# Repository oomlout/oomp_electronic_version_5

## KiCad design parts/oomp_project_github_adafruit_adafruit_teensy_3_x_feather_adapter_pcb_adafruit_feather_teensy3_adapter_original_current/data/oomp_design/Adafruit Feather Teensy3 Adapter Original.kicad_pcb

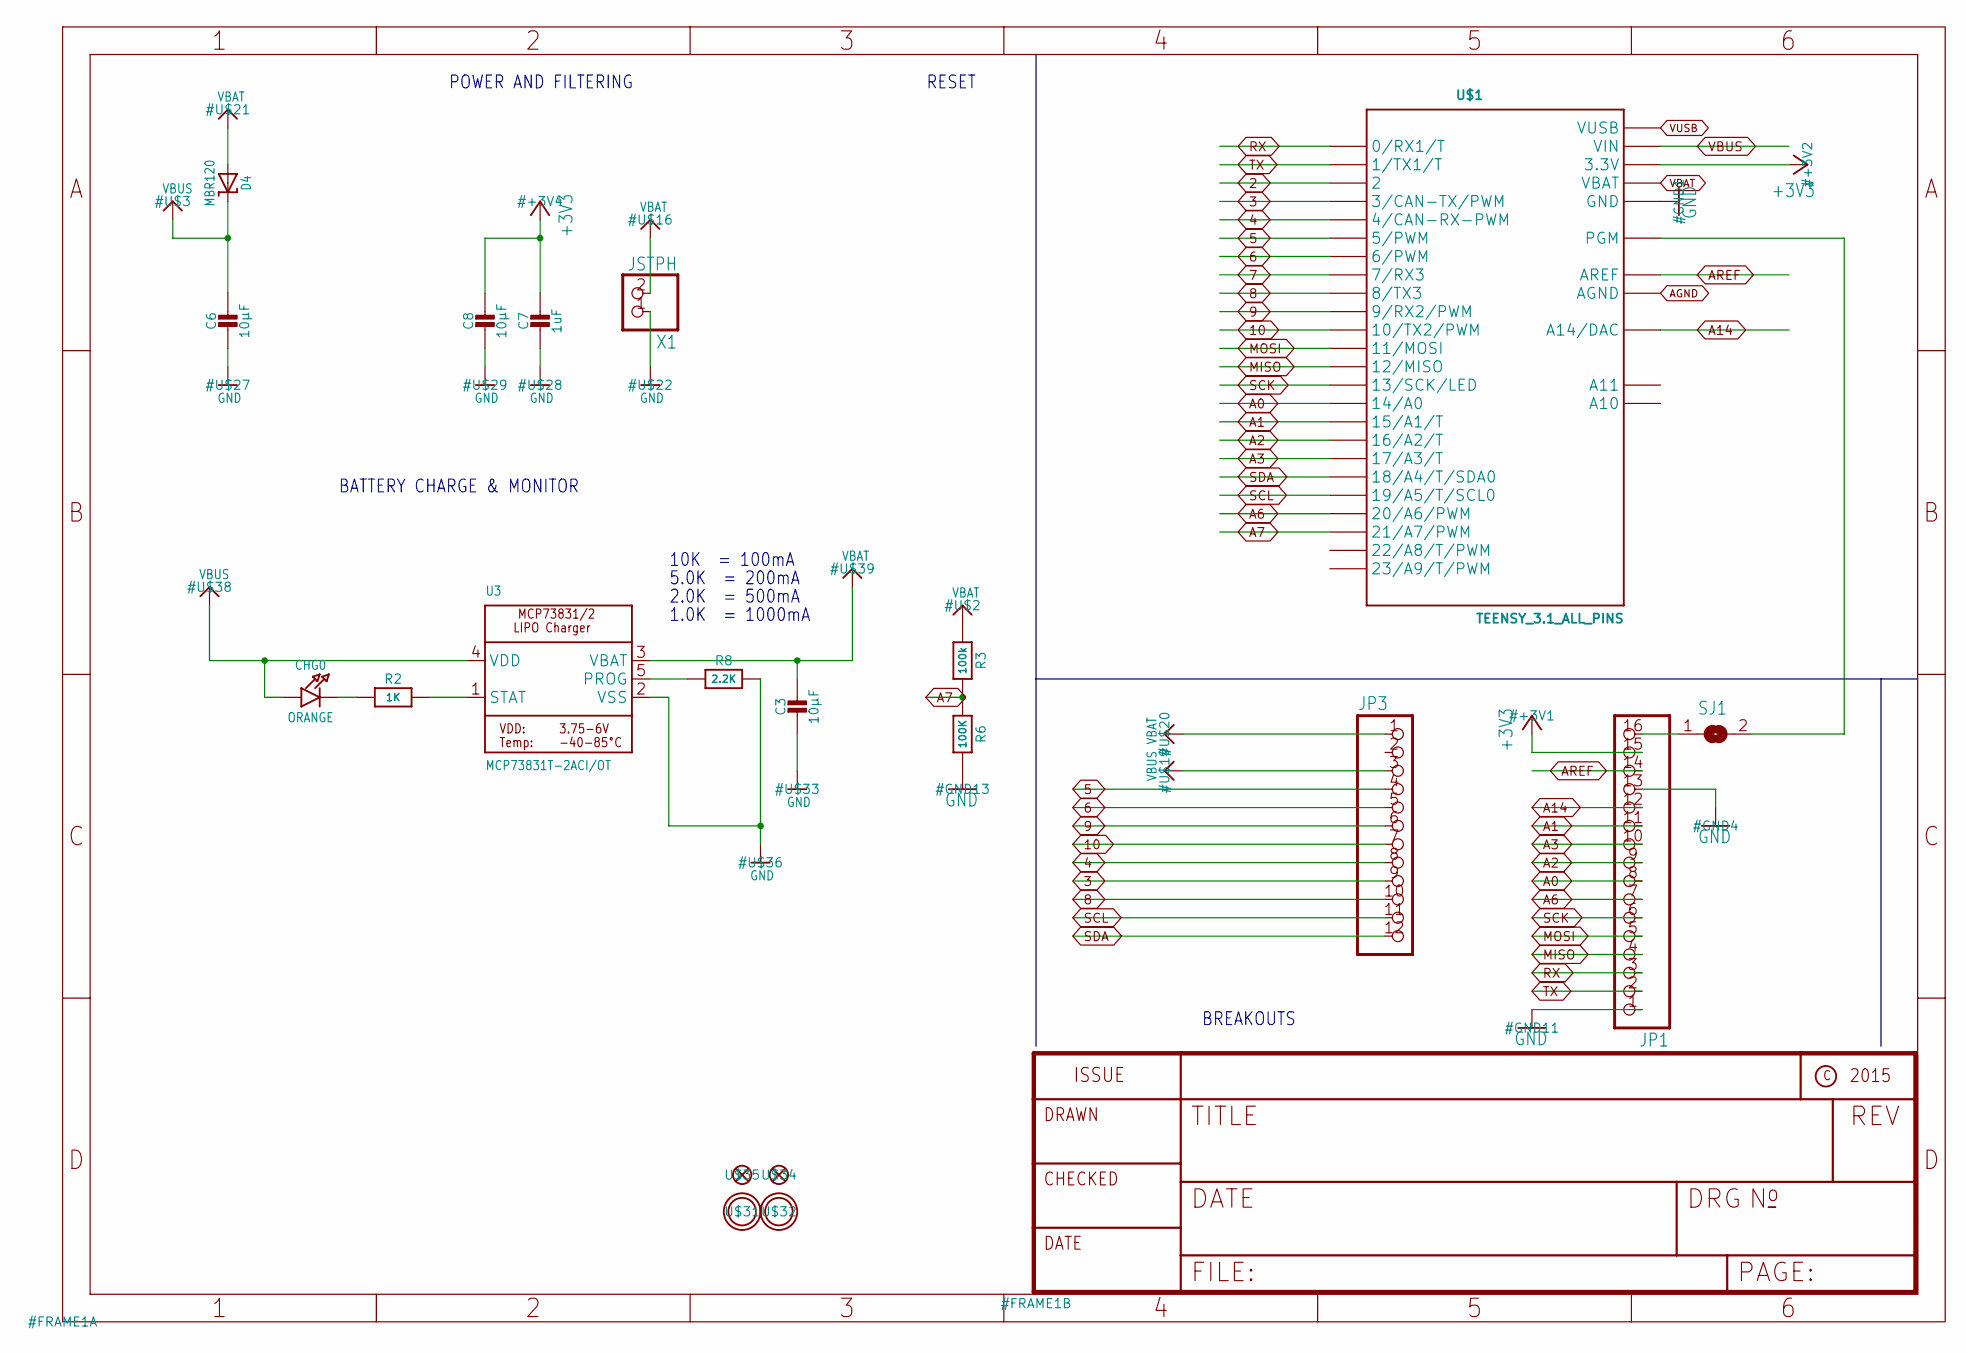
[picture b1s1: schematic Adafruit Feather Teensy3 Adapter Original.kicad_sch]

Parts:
C3, C6, C8: 10µF; 0805-NO
C7: 1uF; 0603-NO
CHG0: ORANGE; CHIPLED_0805_NOOUTLINE
D4: MBR120; SOD-123
JP1: HEADER-1X16ROUND; 1X16_ROUND
JP3: HEADER-1X12; 1X12_ROUND
R2: 1K; 0603-NO
R3: 100k; 0603-NO
R6: 100K; 0603-NO
R8: 2.2K; 0603-NO
SJ1: SOLDERJUMPERCLOSED; SOLDERJUMPER_CLOSEDWIRE
U3: MCP73831T-2ACI/OT; SOT23-5
U$1: TEENSY_3.1_ALL_PINS; TEENSY3-ALL_PINS
U$31, U$32: MOUNTINGHOLE2.5; MOUNTINGHOLE_2.5_PLATED
U$34, U$35: FIDUCIAL""; FIDUCIAL_1MM
X1: JSTPH; JSTPH2

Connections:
2: U$1.2
3: JP3.9, U$1.3 (3/CAN-TX/PWM)
4: JP3.8, U$1.4 (4/CAN-RX-PWM)
5: JP3.4, U$1.5 (5/PWM)
6: JP3.5, U$1.6 (6/PWM)
7: U$1.7 (7/RX3)
8: JP3.10, U$1.8 (8/TX3)
9: JP3.6, U$1.9 (9/RX2/PWM)
10: JP3.7, U$1.10 (10/TX2/PWM)
+3V3: C7.1, C8.1, JP1.15, U$1.3.3V, U$1.3.3V1 (3.3V)
A0: JP1.8, U$1.14/A0
A1: JP1.11, U$1.15/A1 (15/A1/T)
A2: JP1.9, U$1.16/A2 (16/A2/T)
A3: JP1.10, U$1.17/A3 (17/A3/T)
A6: JP1.7, U$1.20/A6 (20/A6/PWM)
A7: R3.2, R6.1, U$1.21/A7 (21/A7/PWM)
A14: JP1.12, U$1.RESET/DAC (A14/DAC)
AGND: U$1.AGND
AREF: JP1.14, U$1.AREF
BOOT: SJ1.2, U$1.PGM
GND: C3.2, C6.2, C7.2, C8.2, JP1.1, JP1.13, R6.2, R8.2, U3.2 (VSS), U$1.GND, U$1.GND1 (GND), X1.1
MISO: JP1.4, U$1.12 (12/MISO)
MOSI: JP1.5, U$1.11 (11/MOSI)
unnamed: CHG0.C, R2.1
unnamed: R2.2, U3.1 (STAT)
unnamed: R8.1, U3.5 (PROG)
RST/BOOT: JP1.16, SJ1.1
RX: JP1.3, U$1.0 (0/RX1/T)
SCK: JP1.6, U$1.13 (13/SCK/LED)
SCL: JP3.11, U$1.19/A5 (19/A5/T/SCL0)
SDA: JP3.12, U$1.18/A4 (18/A4/T/SDA0)
TX: JP1.2, U$1.1 (1/TX1/T)
VBAT: C3.1, D4.A, JP3.1, R3.1, U3.3 (VBAT), U$1.VBAT, X1.2
VBUS: C6.1, CHG0.A, D4.C, JP3.3, U3.4 (VDD), U$1.VIN
VUSB: U$1.VUSB

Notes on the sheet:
BATTERY CHARGE & MONITOR
RESET
2.0K = 500mA
POWER AND FILTERING
BREAKOUTS
1.0K = 1000mA
10K = 100mA
5.0K = 200mA

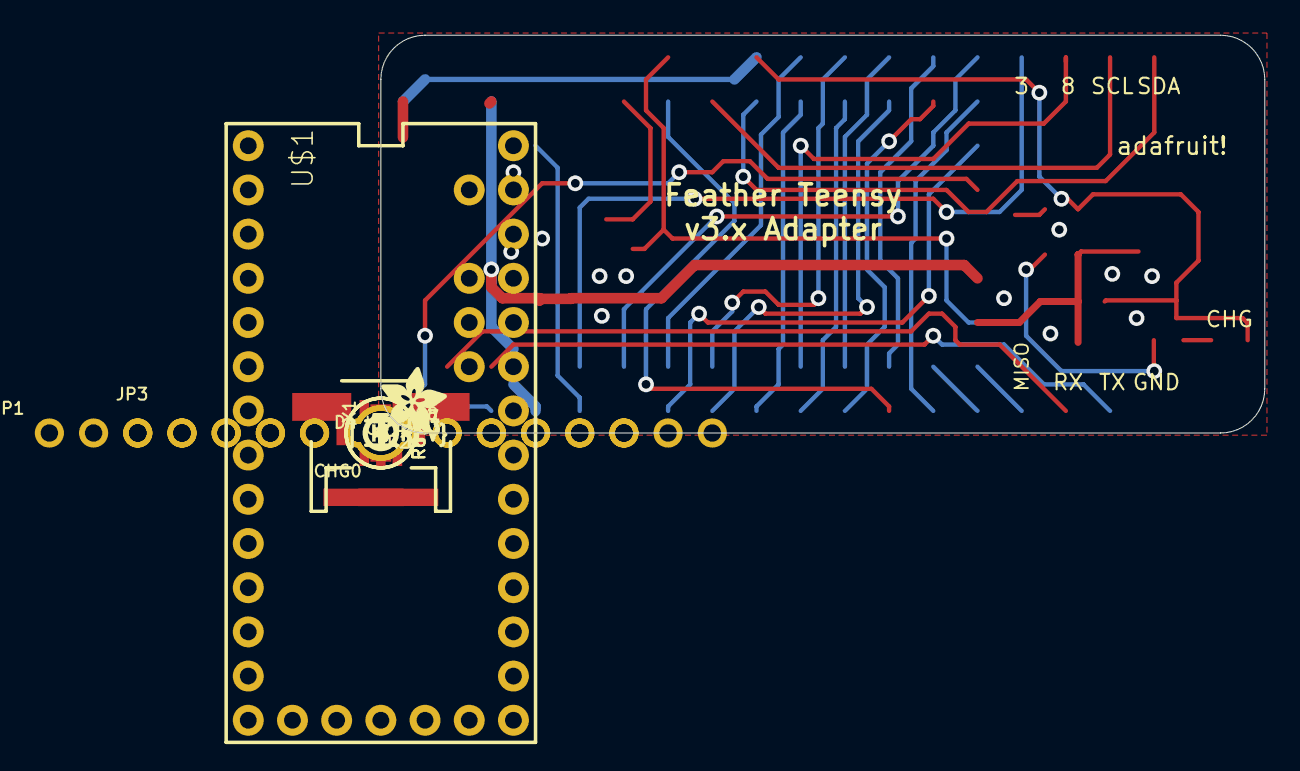
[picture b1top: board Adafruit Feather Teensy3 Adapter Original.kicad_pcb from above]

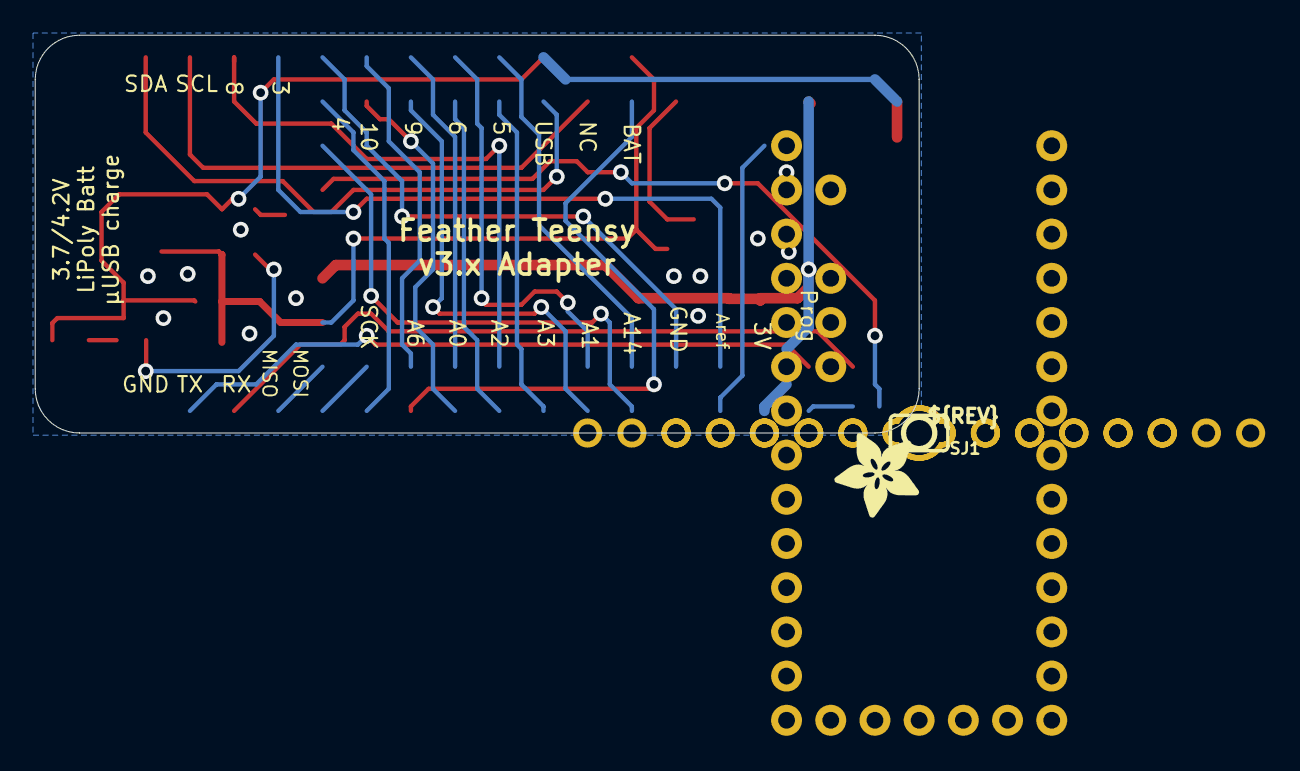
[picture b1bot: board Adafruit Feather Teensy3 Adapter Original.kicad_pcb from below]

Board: 2 copper layers, 50.8 x 22.9 mm, 24 parts (3 on the bottom side), 31 nets.

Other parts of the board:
U$4: ADAFRUIT_5MM
U$5, U$6: PCBFEAT-REV-040
U$7: ADAFRUIT_3.5MM

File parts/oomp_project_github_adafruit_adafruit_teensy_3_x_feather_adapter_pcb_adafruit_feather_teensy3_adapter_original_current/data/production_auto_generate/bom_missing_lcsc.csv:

Designator,Comment,Footprint,OOMP ID,Reason
C3,10µF,Adafruit Feather Teensy3 Adapter Original-import-fps:0805-NO,electronic_capacitor_0805_10_micro_farad,No verified LCSC part number
C6,10µF,Adafruit Feather Teensy3 Adapter Original-import-fps:0805-NO,electronic_capacitor_0805_10_micro_farad,No verified LCSC part number
C8,10µF,Adafruit Feather Teensy3 Adapter Original-import-fps:0805-NO,electronic_capacitor_0805_10_micro_farad,No verified LCSC part number
CHG0,ORANGE,Adafruit Feather Teensy3 Adapter Original-import-fps:CHIPLED_0805_NOOUTLINE,electronic_led_0805,No verified LCSC part number
D4,MBR120,Adafruit Feather Teensy3 Adapter Original-import-fps:SOD-123,,No verified LCSC part number
U3,MCP73831T-2ACI/OT,Adafruit Feather Teensy3 Adapter Original-import-fps:SOT23-5,,No verified LCSC part number
U$1,TEENSY_3.1_ALL_PINS,Adafruit Feather Teensy3 Adapter Original-import-fps:TEENSY3-ALL_PINS,,No verified LCSC part number
U$4,,Adafruit Feather Teensy3 Adapter Original-import-fps:ADAFRUIT_5MM,,No verified LCSC part number
U$5,,Adafruit Feather Teensy3 Adapter Original-import-fps:PCBFEAT-REV-040,,No verified LCSC part number
U$6,,Adafruit Feather Teensy3 Adapter Original-import-fps:PCBFEAT-REV-040,,No verified LCSC part number
U$7,,Adafruit Feather Teensy3 Adapter Original-import-fps:ADAFRUIT_3.5MM,,No verified LCSC part number
U$34,"FIDUCIAL""""",Adafruit Feather Teensy3 Adapter Original-import-fps:FIDUCIAL_1MM,,No verified LCSC part number
U$35,"FIDUCIAL""""",Adafruit Feather Teensy3 Adapter Original-import-fps:FIDUCIAL_1MM,,No verified LCSC part number
X1,JSTPH,Adafruit Feather Teensy3 Adapter Original-import-fps:JSTPH2,,No verified LCSC part number

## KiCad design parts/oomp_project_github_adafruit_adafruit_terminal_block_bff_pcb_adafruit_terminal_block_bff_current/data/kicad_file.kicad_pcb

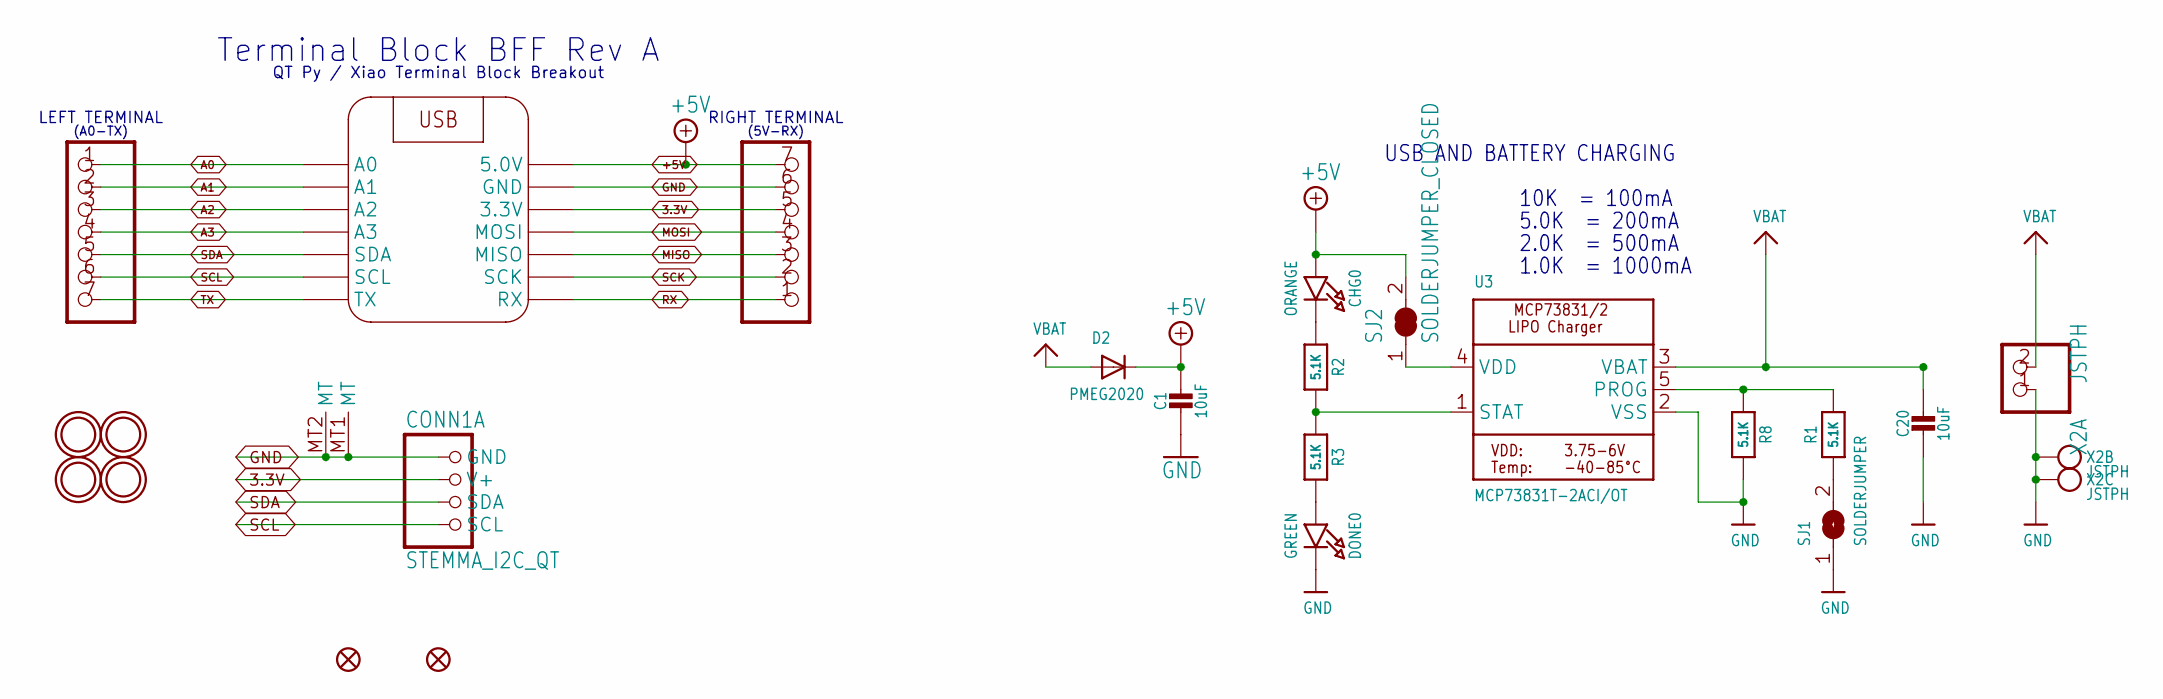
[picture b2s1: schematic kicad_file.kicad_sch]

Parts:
C1, C20: 10uF; 0805-NO
CHG0: ORANGE; CHIPLED_0603_NOOUTLINE
CONN1: STEMMA_I2C_QT; JST_SH4; LCSC C2845363
D2: PMEG2020; SOD-123FL
DONE0: GREEN; CHIPLED_0603_NOOUTLINE
FID1, FID2: FIDUCIAL_0.5MM
JP1, JP2: Terminal; 1X07_2.54MMTERMINAL
R1, R2, R3, R8: 5.1K; _0402NO
SJ1: SOLDERJUMPER; SOLDERJUMPER_ARROW_NOPASTE
SJ2: SOLDERJUMPER_CLOSED; SOLDERJUMPER_CLOSEDWIRE
U3: MCP73831T-2ACI/OT; SOT23-5; JLC_ROTATION 270
U$1, U$2, U$3, U$4: MOUNTINGHOLE2.5; MOUNTINGHOLE_2.5_PLATED
X1: QTPY_SOCKET_DUAL_SMT; QTPY_SMT
X2: JSTPH; JSTPH2_BATT; LCSC C47647

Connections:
3.3V: CONN1.2 (V+), JP1.5, X1.12 (3.3V), X1.12B (3.3V)
+5V: C1.1, CHG0.A, D2.C, JP1.7, SJ2.2, X1.14 (5.0V), X1.14B (5.0V)
A0: JP2.1, X1.1 (A0), X1.1B (A0)
A1: JP2.2, X1.2 (A1), X1.2B (A1)
A2: JP2.3, X1.3 (A2), X1.3B (A2)
A3: JP2.4, X1.4 (A3), X1.4B (A3)
GND: C1.2, C20.2, CONN1.1 (GND), CONN1.MT1 (MT), CONN1.MT2 (MT), DONE0.C, JP1.6, R8.2, SJ1.1, U3.2 (VSS), X1.13 (GND), X1.13B (GND), X2.1, X2.NC1, X2.NC2
MISO: JP1.3, X1.10 (MISO), X1.10B (MISO)
MOSI: JP1.4, X1.11 (MOSI), X1.11B (MOSI)
unnamed: R1.1, SJ1.2
unnamed: CHG0.C, R2.1
unnamed: R2.2, R3.1, U3.1 (STAT)
unnamed: R1.2, R8.1, U3.5 (PROG)
unnamed: DONE0.A, R3.2
unnamed: SJ2.1, U3.4 (VDD)
RX: JP1.1, X1.8 (RX), X1.8B (RX)
SCK: JP1.2, X1.9 (SCK), X1.9B (SCK)
SCL: CONN1.4 (SCL), JP2.6, X1.6 (SCL), X1.6B (SCL)
SDA: CONN1.3 (SDA), JP2.5, X1.5 (SDA), X1.5B (SDA)
TX: JP2.7, X1.7 (TX), X1.7B (TX)
VBAT: C20.1, D2.A, U3.3 (VBAT), X2.2

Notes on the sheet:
5.0K = 200mA
LEFT TERMINAL
1.0K = 1000mA
(A0-TX)
2.0K = 500mA
RIGHT TERMINAL
USB AND BATTERY CHARGING
(5V-RX)
Terminal Block BFF Rev A
10K = 100mA
QT Py / Xiao Terminal Block Breakout

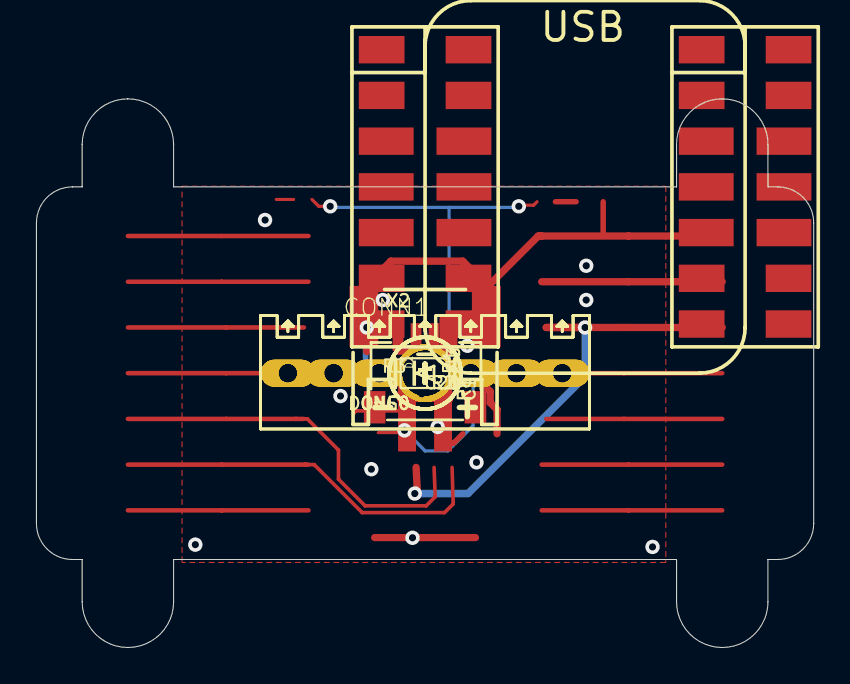
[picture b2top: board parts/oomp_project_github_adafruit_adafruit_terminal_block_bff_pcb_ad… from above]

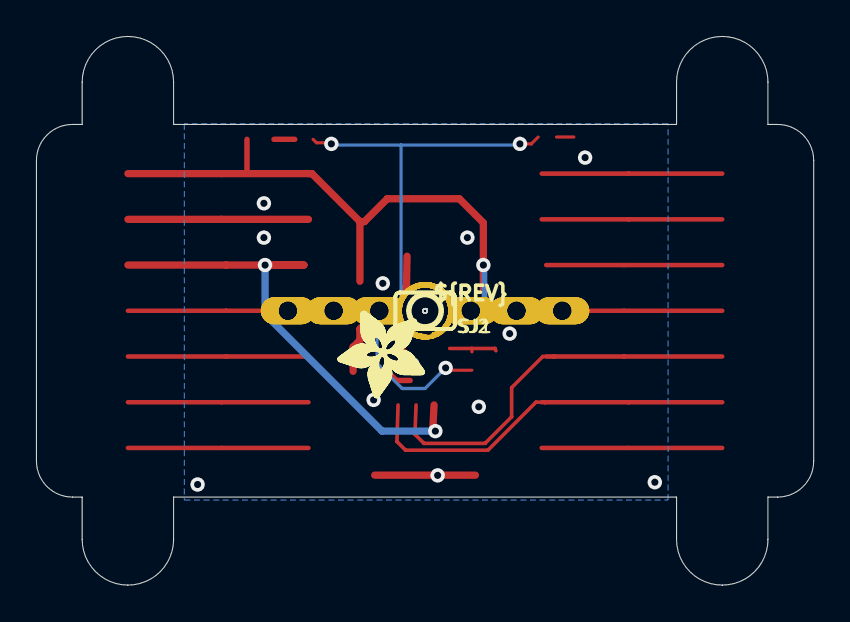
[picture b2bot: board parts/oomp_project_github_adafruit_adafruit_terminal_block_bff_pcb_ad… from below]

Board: 16 copper layers, 43.2 x 30.5 mm, 96 parts (26 on the bottom side), 21 nets.

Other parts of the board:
PLABEL0: PLABEL0
PLABEL1: PLABEL1
PLABEL2: PLABEL2
PLABEL3: PLABEL3
PLABEL4: PLABEL4
PLABEL5: PLABEL5
PLABEL6: PLABEL6
PLABEL7: PLABEL7
PLABEL8: PLABEL8
PLABEL9: PLABEL9
PLABEL10: PLABEL10
PLABEL11: PLABEL11
PLABEL12: PLABEL12
PLABEL13: PLABEL13
PLABEL14: PLABEL14
PLABEL15: PLABEL15
PLABEL16: PLABEL16
PLABEL17: PLABEL17
PLABEL18: PLABEL18
PLABEL19: PLABEL19
PLABEL20: PLABEL20
PLABEL21: PLABEL21
PLABEL22: PLABEL22
PLABEL23: PLABEL23
PLABEL24: PLABEL24
PLABEL25: PLABEL25
PLABEL26: PLABEL26
PLABEL27: PLABEL27
PLABEL28: PLABEL28
PLABEL29: PLABEL29
PLABEL31: PLABEL31
PLABEL32: PLABEL32
PLABEL33: PLABEL33
PLABEL34: PLABEL34
PLABEL35: PLABEL35
PLABEL36: PLABEL36
PLABEL37: PLABEL37
PLABEL38: PLABEL38
U$7, U$8: ADAFRUIT_5MM
U$9: PCBFEAT-REV-040
UNK_HOLE_0: dummyfp0
UNK_HOLE_1: dummyfp1
UNK_HOLE_2: dummyfp2
UNK_HOLE_3: dummyfp3
UNK_HOLE_4: dummyfp4
UNK_HOLE_5: dummyfp5
UNK_HOLE_6: dummyfp6
UNK_HOLE_7: dummyfp7
UNK_HOLE_8: dummyfp8
UNK_HOLE_9: dummyfp9
UNK_HOLE_10: dummyfp10
UNK_HOLE_11: dummyfp11
UNK_HOLE_12: dummyfp12
UNK_HOLE_13: dummyfp13
UNK_HOLE_14: dummyfp14
UNK_HOLE_15: dummyfp15
UNK_HOLE_16: dummyfp16
UNK_HOLE_17: dummyfp17
UNK_HOLE_18: dummyfp18
UNK_HOLE_19: dummyfp19
UNK_HOLE_20: dummyfp20
UNK_HOLE_21: dummyfp21
UNK_HOLE_22: dummyfp22
UNK_HOLE_23: dummyfp23
UNK_HOLE_24: dummyfp24
UNK_HOLE_25: dummyfp25
UNK_HOLE_26: dummyfp26
UNK_HOLE_27: dummyfp27
UNK_HOLE_28: dummyfp28
UNK_HOLE_29: dummyfp29
UNK_HOLE_30: dummyfp30
UNK_HOLE_31: dummyfp31

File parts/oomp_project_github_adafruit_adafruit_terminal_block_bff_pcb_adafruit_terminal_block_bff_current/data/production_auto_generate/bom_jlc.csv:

Comment,Designator,Footprint,LCSC Part #
,"U$7,U$8",Adafruit Terminal Block BFF-import-fps:ADAFRUIT_5MM,
,U$9,Adafruit Terminal Block BFF-import-fps:PCBFEAT-REV-040,
,PLABEL0,Adafruit Terminal Block BFF-import-fps:PLABEL0,
,PLABEL1,Adafruit Terminal Block BFF-import-fps:PLABEL1,
,PLABEL10,Adafruit Terminal Block BFF-import-fps:PLABEL10,
,PLABEL11,Adafruit Terminal Block BFF-import-fps:PLABEL11,
,PLABEL12,Adafruit Terminal Block BFF-import-fps:PLABEL12,
,PLABEL13,Adafruit Terminal Block BFF-import-fps:PLABEL13,
,PLABEL14,Adafruit Terminal Block BFF-import-fps:PLABEL14,
,PLABEL15,Adafruit Terminal Block BFF-import-fps:PLABEL15,
,PLABEL16,Adafruit Terminal Block BFF-import-fps:PLABEL16,
,PLABEL17,Adafruit Terminal Block BFF-import-fps:PLABEL17,
,PLABEL18,Adafruit Terminal Block BFF-import-fps:PLABEL18,
,PLABEL19,Adafruit Terminal Block BFF-import-fps:PLABEL19,
,PLABEL2,Adafruit Terminal Block BFF-import-fps:PLABEL2,
,PLABEL20,Adafruit Terminal Block BFF-import-fps:PLABEL20,
,PLABEL21,Adafruit Terminal Block BFF-import-fps:PLABEL21,
,PLABEL22,Adafruit Terminal Block BFF-import-fps:PLABEL22,
,PLABEL23,Adafruit Terminal Block BFF-import-fps:PLABEL23,
,PLABEL24,Adafruit Terminal Block BFF-import-fps:PLABEL24,
,PLABEL25,Adafruit Terminal Block BFF-import-fps:PLABEL25,
,PLABEL26,Adafruit Terminal Block BFF-import-fps:PLABEL26,
,PLABEL27,Adafruit Terminal Block BFF-import-fps:PLABEL27,
,PLABEL28,Adafruit Terminal Block BFF-import-fps:PLABEL28,
,PLABEL29,Adafruit Terminal Block BFF-import-fps:PLABEL29,
,PLABEL3,Adafruit Terminal Block BFF-import-fps:PLABEL3,
,PLABEL31,Adafruit Terminal Block BFF-import-fps:PLABEL31,
,PLABEL32,Adafruit Terminal Block BFF-import-fps:PLABEL32,
,PLABEL33,Adafruit Terminal Block BFF-import-fps:PLABEL33,
,PLABEL34,Adafruit Terminal Block BFF-import-fps:PLABEL34,
,PLABEL35,Adafruit Terminal Block BFF-import-fps:PLABEL35,
,PLABEL36,Adafruit Terminal Block BFF-import-fps:PLABEL36,
,PLABEL37,Adafruit Terminal Block BFF-import-fps:PLABEL37,
,PLABEL38,Adafruit Terminal Block BFF-import-fps:PLABEL38,
,PLABEL4,Adafruit Terminal Block BFF-import-fps:PLABEL4,
,PLABEL5,Adafruit Terminal Block BFF-import-fps:PLABEL5,
,PLABEL6,Adafruit Terminal Block BFF-import-fps:PLABEL6,
,PLABEL7,Adafruit Terminal Block BFF-import-fps:PLABEL7,
,PLABEL8,Adafruit Terminal Block BFF-import-fps:PLABEL8,
,PLABEL9,Adafruit Terminal Block BFF-import-fps:PLABEL9,
10uF,"C1,C20",Adafruit Terminal Block BFF-import-fps:0805-NO,
5.1K,"R1,R2,R3,R8",Adafruit Terminal Block BFF-import-fps:_0402NO,C25905
GREEN,DONE0,Adafruit Terminal Block BFF-import-fps:CHIPLED_0603_NOOUTLINE,
JSTPH,X2,Adafruit Terminal Block BFF-import-fps:JSTPH2_BATT,
MCP73831T-2ACI/OT,U3,Adafruit Terminal Block BFF-import-fps:SOT23-5,
ORANGE,CHG0,Adafruit Terminal Block BFF-import-fps:CHIPLED_0603_NOOUTLINE,
PMEG2020,D2,Adafruit Terminal Block BFF-import-fps:SOD-123FL,
QTPY_SOCKET_DUAL_SMT,X1,Adafruit Terminal Block BFF-import-fps:QTPY_SMT,
STEMMA_I2C_QT,CONN1,Adafruit Terminal Block BFF-import-fps:JST_SH4,C160404
Terminal,"JP1,JP2",Adafruit Terminal Block BFF-import-fps:1X07_2.54MMTERMINAL,C7501585

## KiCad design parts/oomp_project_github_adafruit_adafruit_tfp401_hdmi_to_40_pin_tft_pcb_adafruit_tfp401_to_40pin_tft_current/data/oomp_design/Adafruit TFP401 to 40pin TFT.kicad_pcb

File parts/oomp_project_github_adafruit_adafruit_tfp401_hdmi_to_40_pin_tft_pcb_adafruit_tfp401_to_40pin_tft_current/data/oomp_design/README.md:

# OOMP KiCad design copy

Open `Adafruit TFP401 to 40pin TFT.kicad_pro` (or the `.kicad_pcb` / `.kicad_sch`) in KiCad. Local OOMP libraries are under `libraries/`. Original inputs are preserved in [../original/](../original/).

Only verified unchanged installed KiCad defaults were renamed. Modified, custom, unmatched and unavailable items remain unchanged. Soldering variants are never swapped during conversion. Existing pad coordinates, nets and UUIDs are preserved.

See [conversion_report.yaml](conversion_report.yaml) for every conversion and skip. Copy this directory before editing; regeneration refuses to overwrite edited design files.

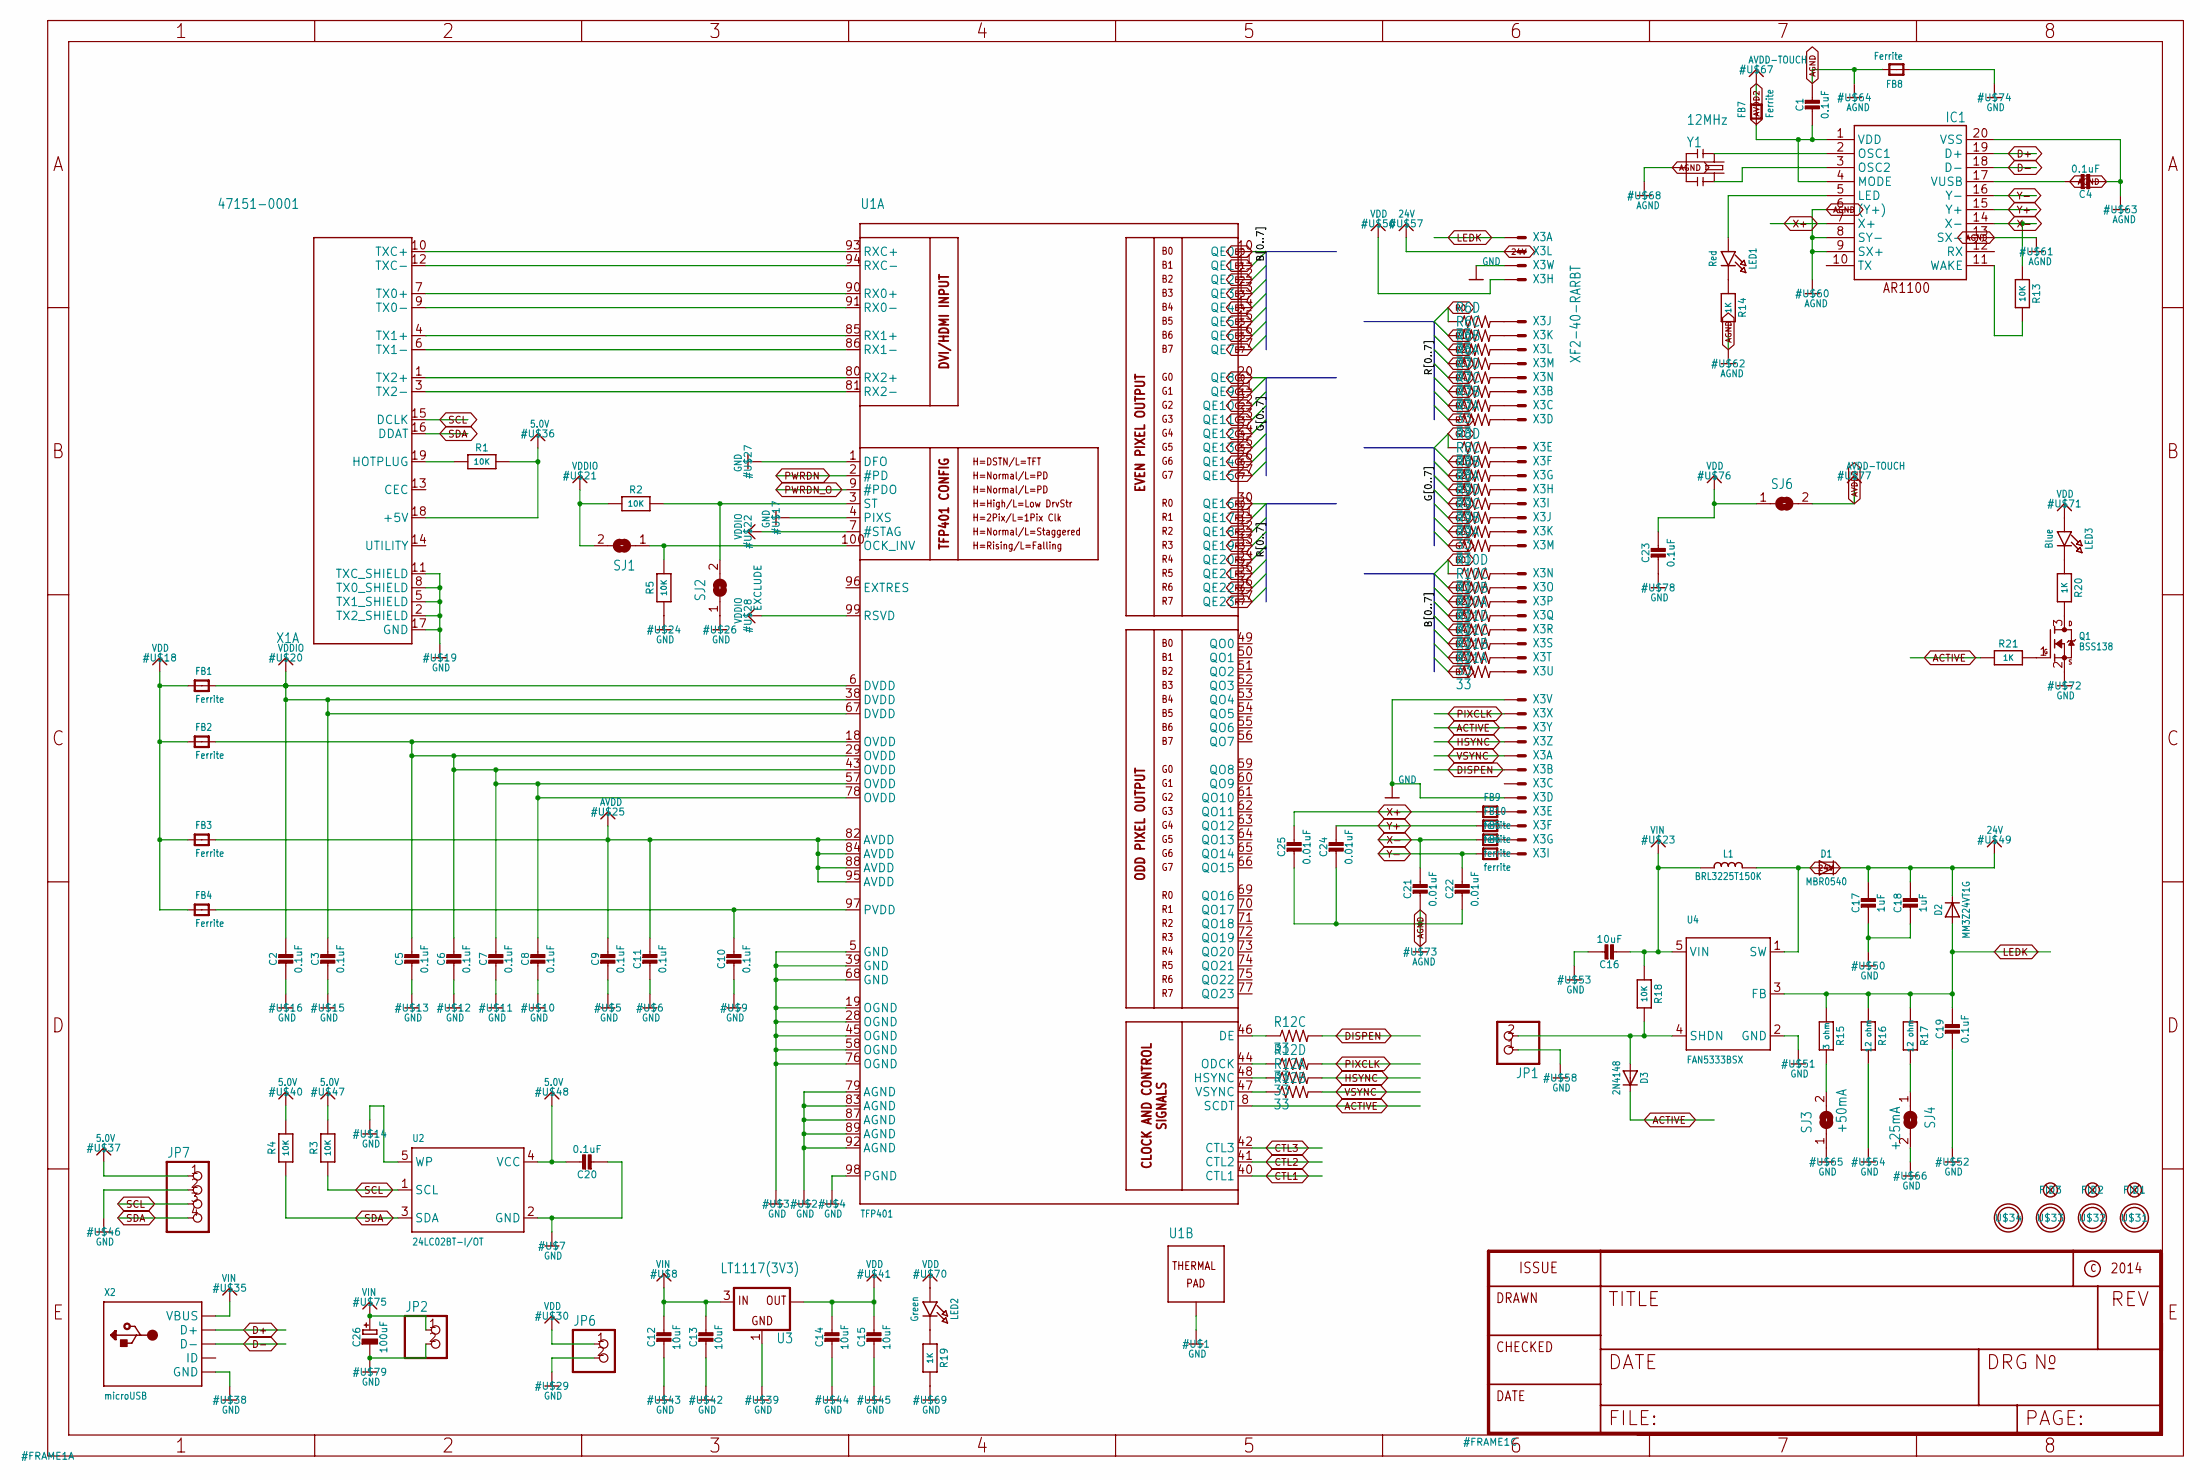
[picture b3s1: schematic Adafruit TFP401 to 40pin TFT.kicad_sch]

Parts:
C1, C2, C3, C4, C5, C7, C8, C9, C10, C11, C19, C20, C23: 0.1uF; 0805-NO
C6: 0.1uF; _0805MP
C12, C13, C14, C15, C16: 10uF; 0805-NO
C17, C18: 1uF; 0805-NO
C21, C22, C24, C25: 0.01uF; 0805-NO
C26: 100uF; PANASONIC_C
D1: MBR0540; SOD-123
D2: MM3Z24VT1G; SMADIODE
D3: 2N4148; SOD-323
FB1, FB2, FB3, FB4, FB7, FB8: Ferrite; _0805MP
FB5, FB6, FB9, FB10: ferrite; _0805MP
FID1, FID2, FID3: FIDUCIAL""; FIDUCIAL_1MM
IC1: AR1100_SSOP; TSSOP20-5.3MMBODY
JP1, JP2, JP6: HEADER-1X2ROUND; 1X02_ROUND
JP7: HEADER-1X476MIL; 1X04_ROUND_76
L1: BRL3225T150K; INDUCTOR_5X5MM_NR5040_NOTHERMALS
LED1: Red; CHIPLED_0805_NOOUTLINE
LED2: Green; CHIPLED_0805_NOOUTLINE
LED3: Blue; CHIPLED_0805_NOOUTLINE
Q1: BSS138; SOT23-R
R1, R2, R3, R4, R18: 10K; 0805-NO
R5, R13: 10K; _0805MP
R6, R7, R8, R9, R10, R11, R12: 33; RESPACK_4X0603
R14, R19, R20, R21: 1K; 0805-NO
R15: 3 ohm; 0805-NO
R16, R17: 12 ohm; 0805-NO
SJ1, SJ2: SOLDERJUMPER; SOLDERJUMPER_ARROW_NOPASTE
SJ3: +50mA; SOLDERJUMPER_ARROW_NOPASTE
SJ4: +25mA; SOLDERJUMPER_ARROW_NOPASTE
SJ6: SOLDERJUMPERCLOSED; SOLDERJUMPER_CLOSEDWIRE
U1: TFP401; S-PQFP-G100
U2: 24LC02BT-I/OT; SOT23-5
U3: LT1117(3V3); SOT223-R
U4: FAN5333BSX; SOT23-5
U$31, U$32, U$33, U$34: MOUNTINGHOLE3.0; MOUNTINGHOLE_3.0_PLATED
X1: 47151-0001; HDMI_MOLEX_47151-0001_DIMLAYER
X2: microUSB; 4UCONN_20329
X3: XF2-40-RARBT; 4-1734839-0
Y1: 12MHz; RESONATOR-SMD

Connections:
5.0V: C20.1, JP7.1, R1.2, R3.2, R4.2, U2.4 (VCC), X1.18 (+5V)
24V: C17.1, C18.1, D1.C, D2.C, X3.2 (MS)
ACTIVE: D3.C, R21.1, U1.8 (SCDT), X3.31 (MS)
AGND: C1.1, C4.2, C21.2, C22.2, C24.2, C25.2, FB8.2, IC1.6 ((Y+)), IC1.8 (SY-), IC1.9 (SX+), IC1.13 (SX-), IC1.20 (VSS), R14.2, Y1.2
ASD: R12.3 (1), U1.46 (DE)
AVDD: C9.1, C11.1, FB3.2, U1.82 (AVDD), U1.84 (AVDD), U1.88 (AVDD), U1.95 (AVDD)
AVDD2: FB7.2, SJ6.2
B0: R10.4 (1), U1.10 (QE0)
B1: R10.3 (1), U1.11 (QE1)
B2: R10.2 (1), U1.12 (QE2)
B3: R10.1, U1.13 (QE3)
B4: R11.4 (1), U1.14 (QE4)
B5: R11.3 (1), U1.15 (QE5)
B6: R11.2 (1), U1.16 (QE6)
B7: R11.1, U1.17 (QE7)
CTL1: U1.40 (CTL1)
CTL2: U1.41 (CTL2)
CTL3: U1.42 (CTL3)
CVB: R12.2 (1), U1.47 (VSYNC)
D+: IC1.19 (D+), X2.D+
D-: IC1.18 (D-), X2.D-
DISPEN: R12.6 (2), X3.34 (MS)
G0: R8.4 (1), U1.20 (QE8)
G1: R8.3 (1), U1.21 (QE9)
G2: R8.2 (1), U1.22 (QE10)
G3: R8.1, U1.23 (QE11)
G4: R9.4 (1), U1.24 (QE12)
G5: R9.3 (1), U1.25 (QE13)
G6: R9.2 (1), U1.26 (QE14)
G7: R9.1, U1.27 (QE15)
GND: C2.2, C3.2, C5.2, C6.2, C7.2, C8.2, C9.2, C10.2, C11.2, C12.2, C13.2, C14.2, C15.2, C16.1, C17.2, C18.2, C19.2, C20.2, C23.2, C26.-, FB8.1, JP1.1, JP2.2, JP6.2, JP7.2, Q1.2 (S), R5.1, R16.2, R19.2, SJ2.1, SJ3.1, SJ4.2, U1.1 (DFO), U1.4 (PIXS), U1.5 (GND), U1.19 (OGND), U1.28 (OGND), U1.39 (GND), U1.45 (OGND), U1.58 (OGND), U1.68 (GND), U1.76 (OGND), U1.79 (AGND), U1.83 (AGND), U1.87 (AGND), U1.89 (AGND), U1.92 (AGND), U1.98 (PGND), U1.P$1 (TP), U1.P$2 (TP), U1.P$3 (TP), U1.P$4 (TP), U1.P$5 (TP), U1.P$6 (TP), U1.P$7 (TP), U1.P$8 (TP), U1.P$9 (TP), U1.P$10 (TP), U1.P$11 (TP), U1.P$12 (TP), U1.P$13 (TP), U1.P$14 (TP), U1.P$15 (TP), U1.P$16 (TP), U1.THERMAL (TP), U2.2 (GND), U2.5 (WP), U3.1 (GND), U4.2 (GND), X1.2 (TX2_SHIELD), X1.5 (TX1_SHIELD), X1.8 (TX0_SHIELD), X1.11 (TXC_SHIELD), X1.17 (GND), X1.P$1 (GND), X1.P$2 (GND), X1.P$3 (GND), X1.P$4 (GND), X2.BASE@1 (GND), X2.BASE@2 (GND), X2.GND, X2.SPRT@1 (GND), X2.SPRT@2 (GND), X2.SPRT@3 (GND), X2.SPRT@4 (GND), X3.3 (MS), X3.29 (MS), X3.36 (MS)
HSYNC: R12.8 (2), X3.32 (MS)
LEDK: C19.1, D2.A, R15.1, R16.1, R17.1, U4.3 (FB), X3.1 (MSV)
unnamed: U1.93 (RXC+), X1.10 (TXC+)
unnamed: U1.94 (RXC-), X1.12 (TXC-)
unnamed: U1.90 (RX0+), X1.7 (TX0+)
unnamed: U1.91 (RX0-), X1.9 (TX0-)
unnamed: U1.85 (RX1+), X1.4 (TX1+)
unnamed: U1.86 (RX1-), X1.6 (TX1-)
unnamed: U1.80 (RX2+), X1.1 (TX2+)
unnamed: U1.81 (RX2-), X1.3 (TX2-)
unnamed: R1.1, X1.19 (HOTPLUG)
unnamed: IC1.2 (OSC1), Y1.1
unnamed: IC1.3 (OSC2), Y1.3
unnamed: C4.1, IC1.17 (VUSB)
unnamed: LED2.C, R19.1
unnamed: R6.5 (2), X3.5 (MS)
unnamed: R6.6 (2), X3.6 (MS)
unnamed: R6.7 (2), X3.7 (MS)
unnamed: R6.8 (2), X3.8 (MS)
unnamed: R7.5 (2), X3.9 (MS)
unnamed: R7.6 (2), X3.10 (MS)
unnamed: R7.7 (2), X3.11 (MS)
unnamed: R7.8 (2), X3.12 (MS)
unnamed: R8.5 (2), X3.13 (MS)
unnamed: R8.6 (2), X3.14 (MS)
unnamed: R8.7 (2), X3.15 (MS)
unnamed: R8.8 (2), X3.16 (MS)
unnamed: R9.5 (2), X3.17 (MS)
unnamed: R9.6 (2), X3.18 (MS)
unnamed: R9.7 (2), X3.19 (MS)
unnamed: R9.8 (2), X3.20 (MS)
unnamed: R10.5 (2), X3.21 (MS)
unnamed: R10.6 (2), X3.22 (MS)
unnamed: R10.7 (2), X3.23 (MS)
unnamed: R10.8 (2), X3.24 (MS)
unnamed: R11.5 (2), X3.25 (MS)
unnamed: R11.6 (2), X3.26 (MS)
unnamed: R11.7 (2), X3.27 (MS)
unnamed: C10.1, FB4.2, U1.97 (PVDD)
unnamed: R11.8 (2), X3.28 (MS)
unnamed: IC1.11 (WAKE), R13.2
unnamed: LED1.C, R14.1
unnamed: C5.1, C6.1, C7.1, C8.1, FB2.2, U1.18 (OVDD), U1.29 (OVDD), U1.43 (OVDD), U1.57 (OVDD), U1.78 (OVDD)
unnamed: IC1.5 (LED), LED1.A
unnamed: LED3.C, R20.1
unnamed: Q1.3 (D), R20.2
unnamed: D1.A, L1.P$2 (2), U4.1 (SW)
unnamed: Q1.1 (G), R21.2
unnamed: R15.2, SJ3.2
unnamed: R17.2, SJ4.1
unnamed: D3.A, JP1.2, R18.2, U4.4 (SHDN)
unnamed: FB5.2, X3.39 (MS)
unnamed: FB6.2, X3.40 (MS)
unnamed: C1.2, FB7.1, IC1.1 (VDD), IC1.4 (MODE)
unnamed: FB9.2, X3.37 (MS)
unnamed: FB10.2, X3.38 (MS)
OCK_INV: R5.2, SJ1.1, U1.100 (OCK_INV)
PIXCLK: R12.5 (2), X3.30 (MS)
PWRDN: U1.2 (#PD)
PWRDN_O: U1.9 (#PDO)
R0: R6.4 (1), U1.30 (QE16)
R1: R6.3 (1), U1.31 (QE17)
R2: R6.2 (1), U1.32 (QE18)
R3: R6.1, U1.33 (QE19)
R4: R7.4 (1), U1.34 (QE20)
R5: R7.3 (1), U1.35 (QE21)
R6: R7.2 (1), U1.36 (QE22)
R7: R7.1, U1.37 (QE23)
SCL: JP7.3, R3.1, U2.1 (SCL), X1.15 (DCLK)
SDA: JP7.4, R4.1, U2.3 (SDA), X1.16 (DDAT)
ST: R2.2, SJ2.2, U1.3 (ST)
VDD: C14.1, C15.1, C23.1, FB1.1, FB2.1, FB3.1, FB4.1, JP6.1, LED2.A, LED3.A, SJ6.1, U3.2 (OUT), U3.4 (OUT), X3.4 (MS)
VDDIO: C2.1, C3.1, FB1.2, R2.1, SJ1.2, U1.6 (DVDD), U1.7 (#STAG), U1.38 (DVDD), U1.67 (DVDD), U1.99 (RSVD)
VIN: C12.1, C13.1, C16.2, C26.+, JP2.1, L1.P$1 (1), R18.1, U3.3 (IN), U4.5 (VIN), X2.VBUS
VSYNC: R12.7 (2), X3.33 (MS)
X+: C25.1, FB9.1, IC1.7 (X+)
X-: C21.1, FB5.1, IC1.14 (X-), R13.1
XCV: R12.1, U1.48 (HSYNC)
Y+: C24.1, FB10.1, IC1.15 (Y+)
Y-: C22.1, FB6.1, IC1.16 (Y-)
ZXC: R12.4 (1), U1.44 (ODCK)
